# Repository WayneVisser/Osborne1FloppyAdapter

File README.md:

Floppy Adapter for the Osborne 1
--------------------------------

1. The Osborne 1 uses a non-standard Shugart-like floppy interface where +12V and +5V for the drive are
fed through the floppy cable.  This KiCAD project accounts for that and creates a nice tidy 
interface to a GoTek floppy disk emulator.  There is no need to modify the Osborne's floppy cable 
as is the case when using a generic floppy adapter.

2. +5V power for the GoTek is taken from the floppy cable.

3. Jumper only S1 on the GoTek.

4. GoTek part number is: SFR1M44-U100K

5. Connector on adapter to mate with GoTek is a Sullins PPPC172LJBN-RC

6. Program the GoTek with FlashFloppy firmware:  https://github.com/keirf/FlashFloppy

**References**

Electrical Details:

* [vcfed](http://www.vcfed.org/forum/showthread.php?56999-Osborne-1-Gotek-Floppy-Emulator-SUCCESS!)

3D printed 3.5" to 5.25" Floppy Case Adapter:

* [thingverse](https://www.thingiverse.com/thing:2217061)

Richard Loxley has done a lot of good work on the Osborne 1.  His site is a *great* resource for
how to get CP/M-formatted floppy disk images working on the GoTek.

* [Richard Loxley](https://www.richardloxley.com/2018/03/30/retro-challenge-2018-04/)

Just want the board?

* [OSHPark](https://oshpark.com/shared_projects/k4YXJYxn)

Some people report that OSHPark may or may not cut the edge connector slot.  So be prepared to dremmel out the slot yourself if they don't!  Alternatively, it may be easier to remove the key from the floppy cable - just make sure you plug the cable into the adapter correctly or there will be smoke!

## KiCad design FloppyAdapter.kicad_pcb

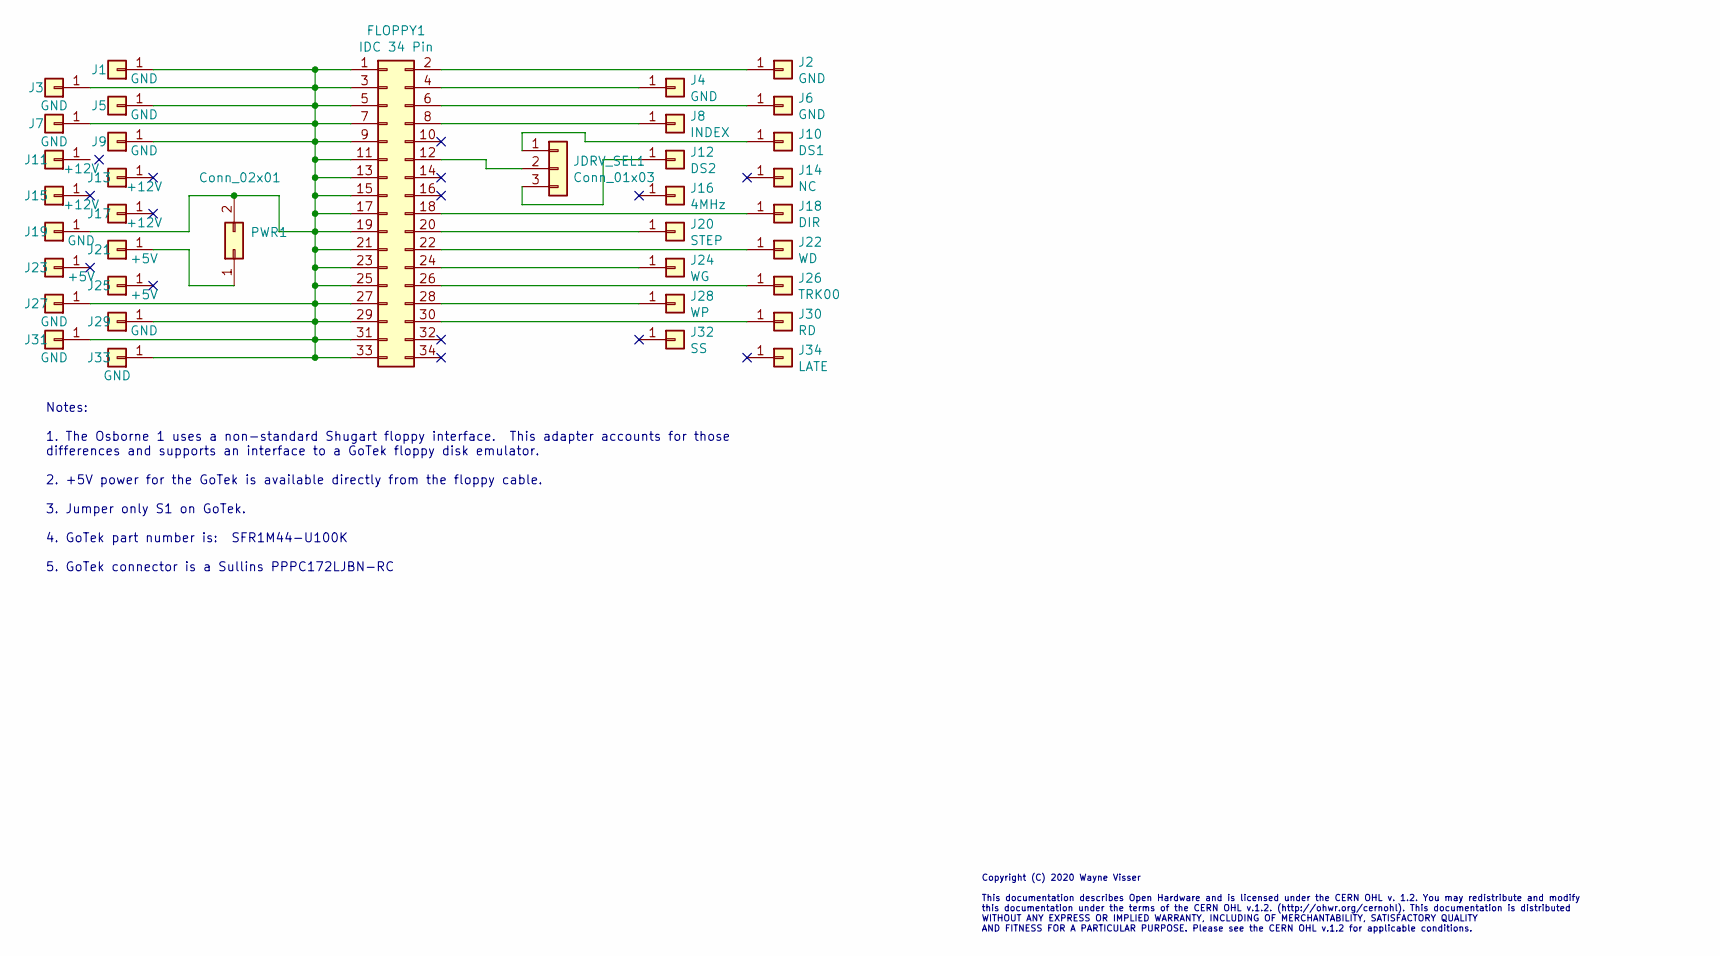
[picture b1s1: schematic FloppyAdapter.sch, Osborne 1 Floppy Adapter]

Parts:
FLOPPY1: IDC 34 Pin; PPPC172LJBN-RC
J1, J2, J3, J4, J5, J6, J7, J9, J19, J27, J29, J31, J33: GND; EdgeFinger
J8: INDEX; EdgeFinger
J10: DS1; EdgeFinger
J11, J13, J15, J17: +12V; EdgeFinger
J12: DS2; EdgeFinger
J14: NC; EdgeFinger
J16: 4MHz; EdgeFinger
J18: DIR; EdgeFinger
J20: STEP; EdgeFinger
J21, J23, J25: +5V; EdgeFinger
J22: WD; EdgeFinger
J24: WG; EdgeFinger
J26: TRK00; EdgeFinger
J28: WP; EdgeFinger
J30: RD; EdgeFinger
J32: SS; EdgeFinger
J34: LATE; EdgeFinger
JDRV_SEL1: Conn_01x03; Pin_Header_Straight_1x03_Pitch2.54mm
PWR1: Conn_02x01; Pin_Header_Straight_1x02_Pitch2.54mm

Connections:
unnamed 0: FLOPPY1.1, FLOPPY1.3, FLOPPY1.5, FLOPPY1.7, FLOPPY1.9, FLOPPY1.11, FLOPPY1.13, FLOPPY1.15, FLOPPY1.17, FLOPPY1.19, FLOPPY1.21, FLOPPY1.23, FLOPPY1.25, FLOPPY1.27, FLOPPY1.29, FLOPPY1.31, FLOPPY1.33, J1.1, J3.1, J5.1, J7.1, J9.1, J19.1, J27.1, J29.1, J31.1, J33.1, PWR1.2; also elsewhere on the board
unnamed 1: FLOPPY1.2, J2.1; also elsewhere on the board
unnamed 2: FLOPPY1.4, J4.1; also elsewhere on the board
unnamed 3: FLOPPY1.6, J6.1; also elsewhere on the board
unnamed 4: FLOPPY1.8, J8.1; also elsewhere on the board
unnamed 6: FLOPPY1.12, JDRV_SEL1.2; also elsewhere on the board
unnamed 9: FLOPPY1.18, J18.1; also elsewhere on the board
unnamed 10: FLOPPY1.20, J20.1; also elsewhere on the board
unnamed 11: FLOPPY1.22, J22.1; also elsewhere on the board
unnamed 12: FLOPPY1.24, J24.1; also elsewhere on the board
unnamed 13: FLOPPY1.26, J26.1; also elsewhere on the board
unnamed 14: FLOPPY1.28, J28.1; also elsewhere on the board
unnamed 15: FLOPPY1.30, J30.1; also elsewhere on the board
unnamed 18: J10.1, JDRV_SEL1.1; also elsewhere on the board
unnamed 20: J12.1, JDRV_SEL1.3; also elsewhere on the board
unnamed: J21.1, PWR1.1

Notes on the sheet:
Copyright (C) 2020 Wayne Visser This documentation describes Open Hardware and is licensed under the CERN OHL v. 1.2. You may redistribute and modify this documentation under the terms of the CERN OHL v.1.2. (http://ohwr.org/cernohl). This documentation is distributed WITHOUT ANY EXPRESS OR IMPLIED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
Notes: 1. The Osborne 1 uses a non-standard Shugart floppy interface. This adapter accounts for those differences and supports an interface to a GoTek floppy disk emulator. 2. +5V power for the GoTek is available directly from the floppy cable. 3. Jumper only S1 on GoTek. 4. GoTek part number is: S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

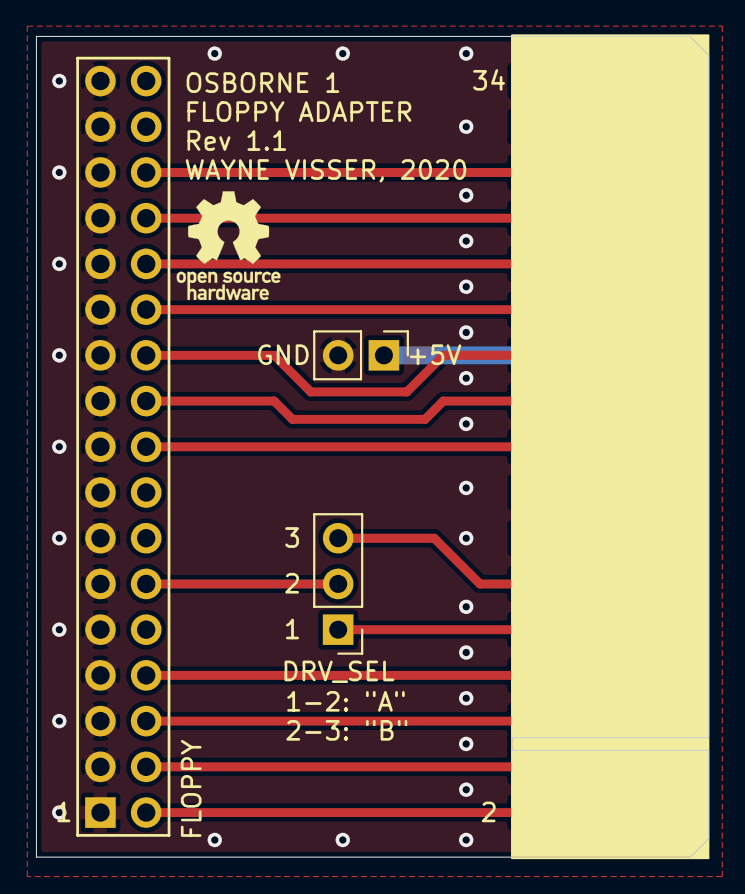
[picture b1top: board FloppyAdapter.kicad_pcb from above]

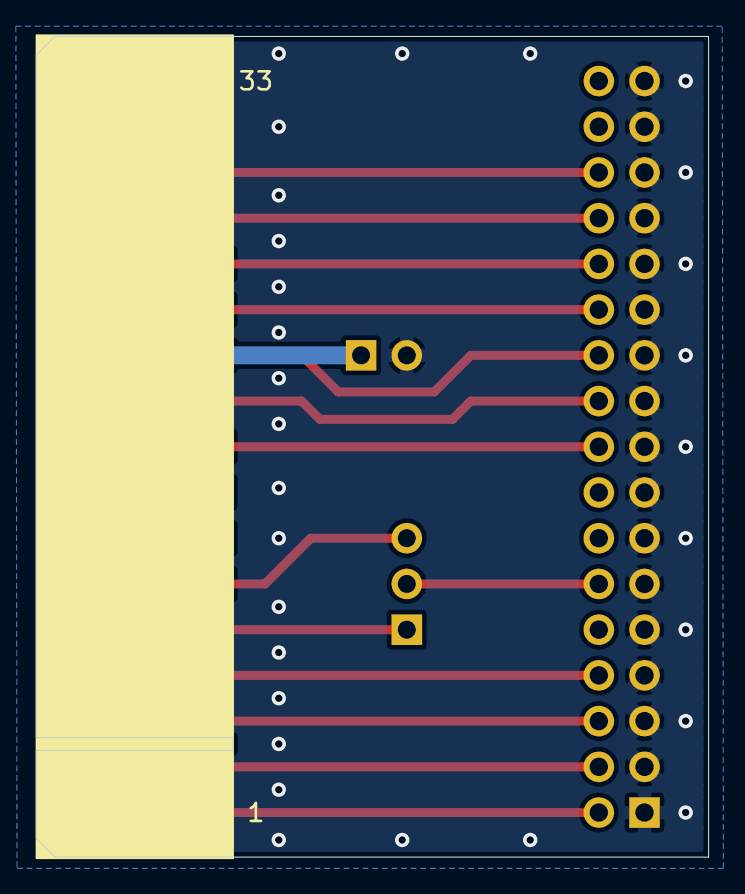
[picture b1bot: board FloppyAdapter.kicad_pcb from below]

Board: 2 copper layers, 37.3 x 45.6 mm, 37 parts (17 on the bottom side), 16 nets.

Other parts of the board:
DRV_SEL: Conn_01x03; Pin_Header_Straight_1x03_Pitch2.54mm
FLOPPY: IDC 34 Pin; PPPC172LJBN-RC

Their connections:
unnamed 0: FLOPPY.1, FLOPPY.3, FLOPPY.5, FLOPPY.7, FLOPPY.9, FLOPPY.11, FLOPPY.13, FLOPPY.15, FLOPPY.17, FLOPPY.19, FLOPPY.21, FLOPPY.23, FLOPPY.25, FLOPPY.27, FLOPPY.29, FLOPPY.31, FLOPPY.33; also elsewhere on the board
unnamed 1: FLOPPY.2; also elsewhere on the board
unnamed 2: FLOPPY.4; also elsewhere on the board
unnamed 3: FLOPPY.6; also elsewhere on the board
unnamed 4: FLOPPY.8; also elsewhere on the board
unnamed 6: DRV_SEL.2, FLOPPY.12; also elsewhere on the board
unnamed 9: FLOPPY.18; also elsewhere on the board
unnamed 10: FLOPPY.20; also elsewhere on the board
unnamed 11: FLOPPY.22; also elsewhere on the board
unnamed 12: FLOPPY.24; also elsewhere on the board
unnamed 13: FLOPPY.26; also elsewhere on the board
unnamed 14: FLOPPY.28; also elsewhere on the board
unnamed 15: FLOPPY.30; also elsewhere on the board
unnamed 18: DRV_SEL.1; also elsewhere on the board
unnamed 20: DRV_SEL.3; also elsewhere on the board

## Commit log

2021-05-29 Update README.md
    Add OSHPark note.
